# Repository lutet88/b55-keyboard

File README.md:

# b55-keyboard
55-key 4x14.5u keyboard pcb/project/ic

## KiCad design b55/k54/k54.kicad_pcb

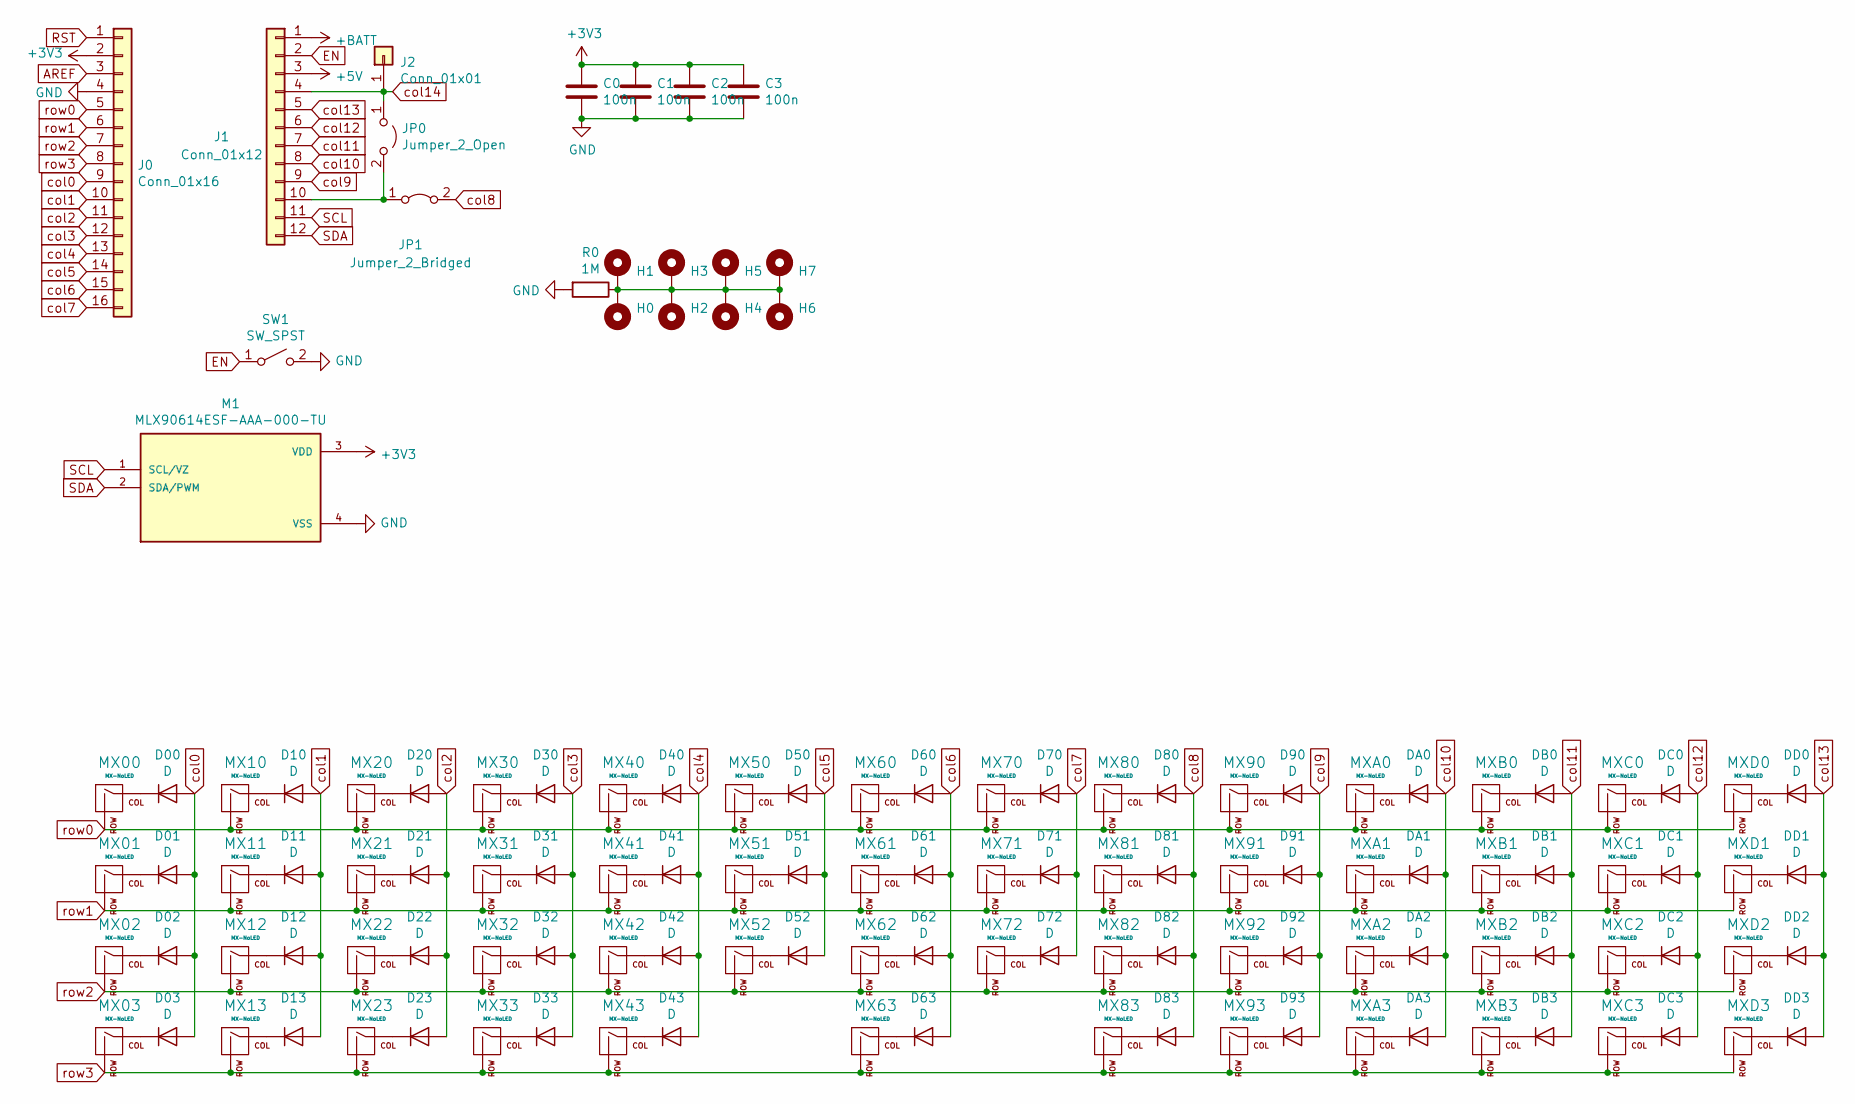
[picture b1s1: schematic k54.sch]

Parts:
C0, C1, C2, C3: 100n; C_0805_2012Metric_Pad1.15x1.40mm_HandSolder
D00, D01, D02, D03, D10, D11, D12, D13, D20, D21, D22, D23, D30, D31, D32, D33, D40, D41, D42, D43, D50, D51, D52, D60, D61, D62, D63, D70, D71, D72, D80, D81, D82, D83, D90, D91, D92, D93: D; D_SOT-23_ANK
DA0, DA1, DA2, DA3: D; D_SOT-23_ANK
DB0, DB1, DB2, DB3: D; D_SOT-23_ANK
DC0, DC1, DC2, DC3: D; D_SOT-23_ANK
DD0, DD1, DD2, DD3: D; D_SOT-23_ANK
H0, H1, H2, H3, H4, H5, H6, H7: MountingHole_Pad; MountingHole_2.7mm_M2.5_ISO7380_Pad
J0: Conn_01x16; PinHeader_1x16_P2.54mm_Vertical
J1: Conn_01x12; PinHeader_1x12_P2.54mm_Vertical
J2: Conn_01x01; PinHeader_1x01_P2.54mm_Vertical
JP0: Jumper_2_Open; SolderJumper-2_P1.3mm_Open_Pad1.0x1.5mm
JP1: Jumper_2_Bridged; SolderJumper-2_P1.3mm_Bridged_Pad1.0x1.5mm
M1: MLX90614ESF-AAA-000-TU; TO254P942H425-4; PARTREV 13
MX00, MX10, MX11, MX12, MX13, MX20, MX21, MX22, MX23, MX30, MX31, MX32, MX33, MX40, MX41, MX42, MX50, MX51, MX52, MX60, MX61, MX62, MX70, MX71, MX72, MX80, MX81, MX82, MX83, MX90, MX91, MX92, MX93: MX-NoLED; SW_Cherry_MX_1.00u_PCB
MX01, MX03: MX-NoLED; SW_Cherry_MX_1.25u_PCB
MX02: MX-NoLED; SW_Cherry_MX_1.75u_PCB
MX43, MX63: MX-NoLED; SW_Cherry_MX_2.25u_PCB
MXA0, MXA1, MXA2, MXA3: MX-NoLED; SW_Cherry_MX_1.00u_PCB
MXB0, MXB1, MXB2, MXB3: MX-NoLED; SW_Cherry_MX_1.00u_PCB
MXC0, MXC2, MXC3: MX-NoLED; SW_Cherry_MX_1.00u_PCB
MXC1: MX-NoLED; SW_Cherry_MX_1.50u_PCB
MXD0: MX-NoLED; SW_Cherry_MX_1.75u_PCB
MXD1, MXD2, MXD3: MX-NoLED; SW_Cherry_MX_1.00u_PCB
R0: 1M; R_0815_2038Metric_Pad1.53x4.00mm_HandSolder
SW1: SW_SPST; PinHeader_1x02_P2.54mm_Vertical

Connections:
+3V3: C0.1, C1.1, C2.1, C3.1, J0.2, M1.3 (VDD)
+5V: J1.3
+BATT: J1.1
AREF: J0.3
EN: J1.2, SW1.1 (A)
GND: C0.2, C1.2, C2.2, C3.2, J0.4, M1.4 (VSS), R0.2, SW1.2 (B)
unnamed: D00.1 (K), MX00.1 (COL)
unnamed: D01.1 (K), MX01.1 (COL)
unnamed: D02.1 (K), MX02.1 (COL)
unnamed: D03.1 (K), MX03.1 (COL)
unnamed: D10.1 (K), MX10.1 (COL)
unnamed: D11.1 (K), MX11.1 (COL)
unnamed: D12.1 (K), MX12.1 (COL)
unnamed: D13.1 (K), MX13.1 (COL)
unnamed: D20.1 (K), MX20.1 (COL)
unnamed: D21.1 (K), MX21.1 (COL)
unnamed: D22.1 (K), MX22.1 (COL)
unnamed: D23.1 (K), MX23.1 (COL)
unnamed: D30.1 (K), MX30.1 (COL)
unnamed: D31.1 (K), MX31.1 (COL)
unnamed: D32.1 (K), MX32.1 (COL)
unnamed: D33.1 (K), MX33.1 (COL)
unnamed: D40.1 (K), MX40.1 (COL)
unnamed: D41.1 (K), MX41.1 (COL)
unnamed: D42.1 (K), MX42.1 (COL)
unnamed: D43.1 (K), MX43.1 (COL)
unnamed: D50.1 (K), MX50.1 (COL)
unnamed: D51.1 (K), MX51.1 (COL)
unnamed: D52.1 (K), MX52.1 (COL)
unnamed: D60.1 (K), MX60.1 (COL)
unnamed: D61.1 (K), MX61.1 (COL)
unnamed: D62.1 (K), MX62.1 (COL)
unnamed: D63.1 (K), MX63.1 (COL)
unnamed: D70.1 (K), MX70.1 (COL)
unnamed: D71.1 (K), MX71.1 (COL)
unnamed: D72.1 (K), MX72.1 (COL)
unnamed: D80.1 (K), MX80.1 (COL)
unnamed: D81.1 (K), MX81.1 (COL)
unnamed: D82.1 (K), MX82.1 (COL)
unnamed: D83.1 (K), MX83.1 (COL)
unnamed: D90.1 (K), MX90.1 (COL)
unnamed: D91.1 (K), MX91.1 (COL)
unnamed: D92.1 (K), MX92.1 (COL)
unnamed: D93.1 (K), MX93.1 (COL)
unnamed: DA0.1 (K), MXA0.1 (COL)
unnamed: DA1.1 (K), MXA1.1 (COL)
unnamed: DA2.1 (K), MXA2.1 (COL)
unnamed: DA3.1 (K), MXA3.1 (COL)
unnamed: DB0.1 (K), MXB0.1 (COL)
unnamed: DB1.1 (K), MXB1.1 (COL)
unnamed: DB2.1 (K), MXB2.1 (COL)
unnamed: DB3.1 (K), MXB3.1 (COL)
unnamed: DC0.1 (K), MXC0.1 (COL)
unnamed: DC1.1 (K), MXC1.1 (COL)
unnamed: DC2.1 (K), MXC2.1 (COL)
unnamed: DC3.1 (K), MXC3.1 (COL)
unnamed: DD0.1 (K), MXD0.1 (COL)
unnamed: DD1.1 (K), MXD1.1 (COL)
unnamed: DD2.1 (K), MXD2.1 (COL)
unnamed: DD3.1 (K), MXD3.1 (COL)
unnamed: H0.1, H1.1, H2.1, H3.1, H4.1, H5.1, H6.1, H7.1, R0.1
unnamed: J1.10, JP0.2 (B), JP1.1 (A)
RST: J0.1
SCL: J1.11, M1.1 (SCL/VZ)
SDA: J1.12, M1.2 (SDA/PWM)
col0: D00.2 (A), D01.2 (A), D02.2 (A), D03.2 (A), J0.9
col1: D10.2 (A), D11.2 (A), D12.2 (A), D13.2 (A), J0.10
col2: D20.2 (A), D21.2 (A), D22.2 (A), D23.2 (A), J0.11
col3: D30.2 (A), D31.2 (A), D32.2 (A), D33.2 (A), J0.12
col4: D40.2 (A), D41.2 (A), D42.2 (A), D43.2 (A), J0.13
col5: D50.2 (A), D51.2 (A), D52.2 (A), J0.14
col6: D60.2 (A), D61.2 (A), D62.2 (A), D63.2 (A), J0.15
col7: D70.2 (A), D71.2 (A), D72.2 (A), J0.16
col8: D80.2 (A), D81.2 (A), D82.2 (A), D83.2 (A), JP1.2 (B)
col9: D90.2 (A), D91.2 (A), D92.2 (A), D93.2 (A), J1.9
col10: DA0.2 (A), DA1.2 (A), DA2.2 (A), DA3.2 (A), J1.8
col11: DB0.2 (A), DB1.2 (A), DB2.2 (A), DB3.2 (A), J1.7
col12: DC0.2 (A), DC1.2 (A), DC2.2 (A), DC3.2 (A), J1.6
col13: DD0.2 (A), DD1.2 (A), DD2.2 (A), DD3.2 (A), J1.5
col14: J1.4, J2.1, JP0.1 (A)
row0: J0.5, MX00.2 (ROW), MX10.2 (ROW), MX20.2 (ROW), MX30.2 (ROW), MX40.2 (ROW), MX50.2 (ROW), MX60.2 (ROW), MX70.2 (ROW), MX80.2 (ROW), MX90.2 (ROW), MXA0.2 (ROW), MXB0.2 (ROW), MXC0.2 (ROW), MXD0.2 (ROW)
row1: J0.6, MX01.2 (ROW), MX11.2 (ROW), MX21.2 (ROW), MX31.2 (ROW), MX41.2 (ROW), MX51.2 (ROW), MX61.2 (ROW), MX71.2 (ROW), MX81.2 (ROW), MX91.2 (ROW), MXA1.2 (ROW), MXB1.2 (ROW), MXC1.2 (ROW), MXD1.2 (ROW)
row2: J0.7, MX02.2 (ROW), MX12.2 (ROW), MX22.2 (ROW), MX32.2 (ROW), MX42.2 (ROW), MX52.2 (ROW), MX62.2 (ROW), MX72.2 (ROW), MX82.2 (ROW), MX92.2 (ROW), MXA2.2 (ROW), MXB2.2 (ROW), MXC2.2 (ROW), MXD2.2 (ROW)
row3: J0.8, MX03.2 (ROW), MX13.2 (ROW), MX23.2 (ROW), MX33.2 (ROW), MX43.2 (ROW), MX63.2 (ROW), MX83.2 (ROW), MX93.2 (ROW), MXA3.2 (ROW), MXB3.2 (ROW), MXC3.2 (ROW), MXD3.2 (ROW)

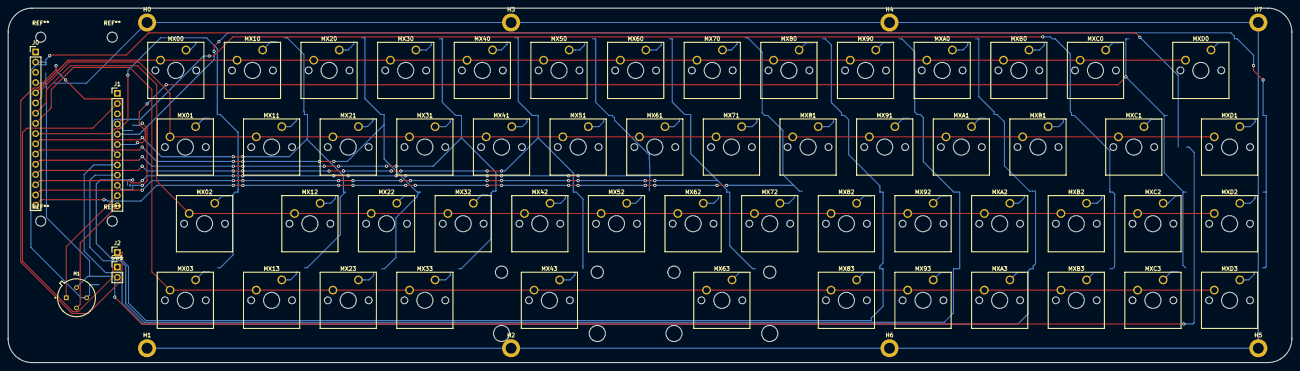
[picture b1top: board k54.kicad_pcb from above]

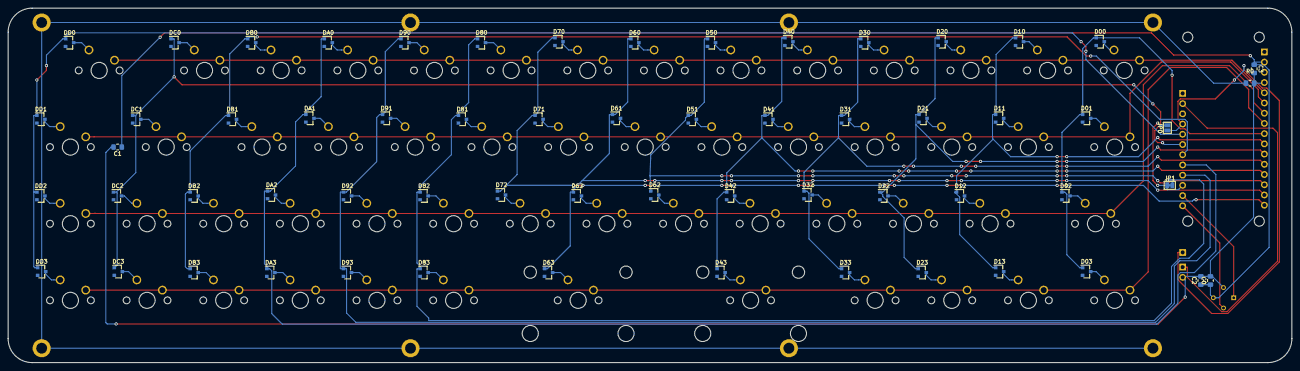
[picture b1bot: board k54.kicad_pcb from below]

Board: 2 copper layers, 319.1 x 88.1 mm, 128 parts (61 on the bottom side), 80 nets.

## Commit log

2021-01-12 initial schematic
2021-01-28 i have no fucking idea
    please help
